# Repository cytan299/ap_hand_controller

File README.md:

# A simple hand controller for Astro-Physics mounts

by C.Y. Tan 2018

It is well-known, that the new GTOCP4 control box can be controlled
with a phone or a pad. However, I really like the feel of real buttons
in a controller rather than using "virtual" buttons on a phone or pad.
This means that the only solution that Astro-Physics (AP) has for people like
me is to buy their AP keypad.

If I had the AP keypad, I will mainly use it for Polar aligning with
PoleMaster and for recalibrating (which is the same as syncing for all
other mounts). After polar alignment and recalibrating, PHD2 will be
used for guiding the scope. Therefore, the AP keypad will only be used
at the start of my imaging session, and no more. Thus, it is hard for
me to justify spending $1000 for an AP keypad when I will hardly use.
I had to figure out a solution.

And here's my solution:
* I have built a simple hand controller for my Mach1GTO. Its purpose
is **not** to replace the AP keypad because it does not initialize the
CP4, have any star database or goto capability etc. My goal is to just
move the mount for calibrating the mount to a star and be compatible
with PoleMaster.

## Design

The goal of my hand controller is to be low cost (less than $200). The
simplest way I know how to do this is to base it on an
[Arduino controller](https://www.sparkfun.com/products/12640). The
other low cost components are

* A small 64x48
  [OLED display](https://www.ebay.com/itm/0-66-OLED-Display-Module-7pin-64x48-Screen-SPI-I2C-3-3-5V-for-Arduino-AVR-STM32/311968961516?_trkparms=aid%3D111001%26algo%3DREC.SEED%26ao%3D1%26asc%3D51025%26meid%3Dd4485726d0e34c16a699dcc92951db6e%26pid%3D100675%26rk%3D5%26rkt%3D15%26sd%3D323141166313%26itm%3D311968961516&_trksid=p2481888.c100675.m4236&_trkparms=pageci%3Ada1189f9-3ac9-11e8-906e-74dbd1800d52%7Cparentrq%3Aa2cf6cb51620ab6ac78552f3fffc49d7%7Ciid%3A1)
  for showing the user options and the state of the controller.
* A [thumb joystick](https://www.sparkfun.com/products/9032) for
selecting menu items and for moving the telescope in RA and DEC.
* The hand controller will be connected to the same port that the AP
  keypad uses. 

## Support

This is unsupported hardware. Build at your own peril! :)

You can submit questions or bug reports using the
[issues](https://github.com/cytan299/ap_hand_controller/issues) tab on
the right and then click on **NEW**.

Have fun!

## Directory structure

* **howto** Assembly instructions for the hand controller.
* **ponoko** The files that are used for laser cutting the acrylic parts of
the design. These files can be sent directly to
[Ponoko](http://www.ponoko.com) for laser cutting.
* **bom** Bill of materials for one hand controller.
* **eagle** Eagle schematic and board files.
* **arduino** Source code for the hand controller.
* **pics** Photographs used in the README's and Wiki.
* **user manual** contains the hand controller user manual.

## Other information

More information can be found in he *README.md* files in each
directory and the [wiki](https://github.com/cytan299/ap_hand_controller/wiki/A-simple-hand-controller-for-Astro-Physics-mounts) of this project on github.

## Copyright
All the software, documentation, and hardware that I have written is
copyright 2018 C.Y. Tan.

All software is released under GPLv3

All documentation is released under:
* Creative Commons Attribution-ShareAlike 3.0 Unported License
* GNU Free Documentation License, Version 1.3
* Creative Commons Attribution-ShareAlike 4.0 International License

All hardware is released under CERN Hardware Open License v1.2

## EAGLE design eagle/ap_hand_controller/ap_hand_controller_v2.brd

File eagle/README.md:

# Eagle files

These are the eagle files that can be sent to pc board manufacturers to
be made. There is a free version of [eagle](http://cadsoftusa.com)
that can be downloaded to view the designs.

## Directories

* **ap_hand_controller** The hand controller unit schematic and pcb.

## Copyright

The schematic and board designs are copyright 2018 C.Y. Tan and
released under the CERN Open Hardware License v1.2

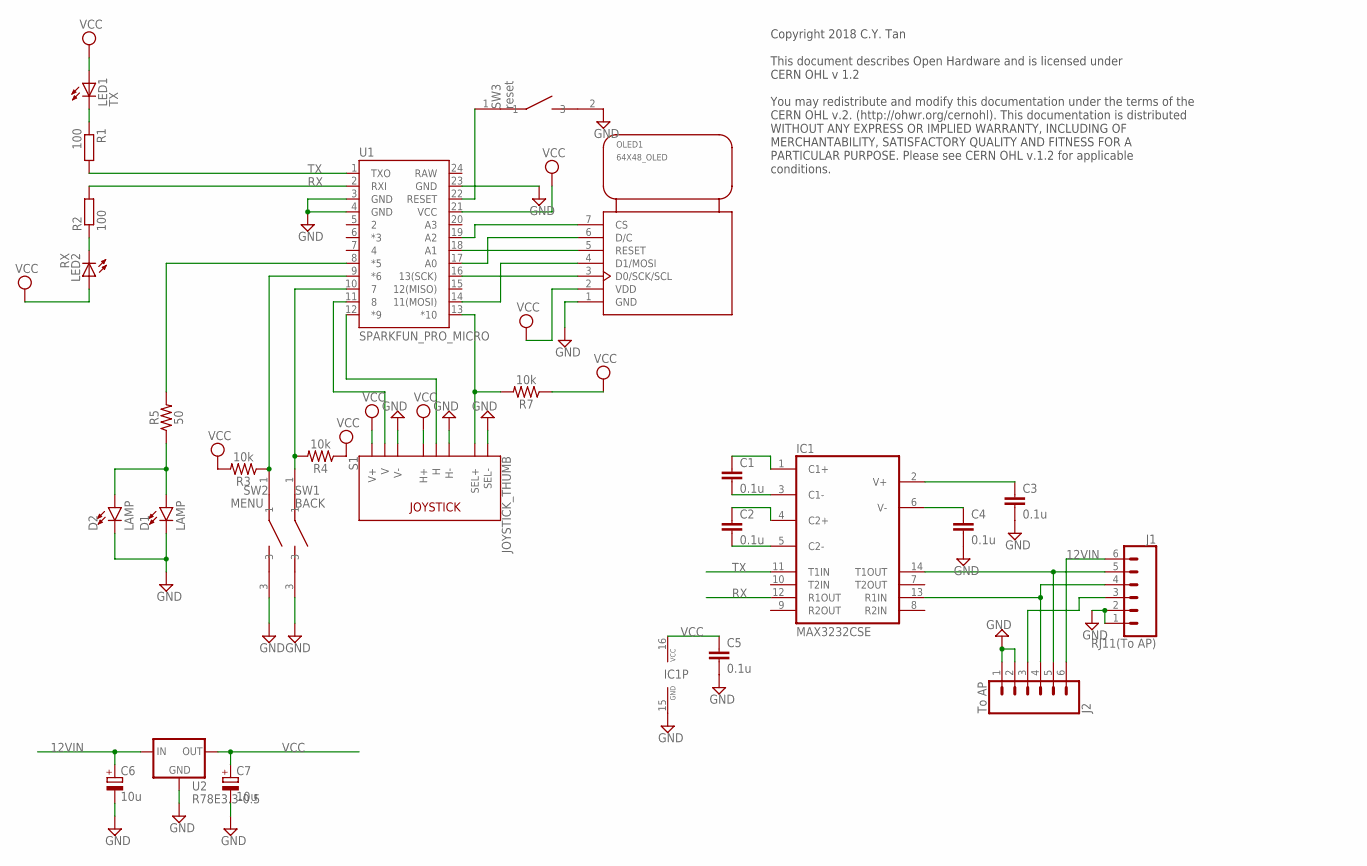
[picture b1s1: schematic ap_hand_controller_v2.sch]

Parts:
C1, C2, C3, C4, C5: 0.1u; C1206
C6, C7: 10u; E2,5-6
D1, D2: LAMP; LED_5MM
IC1: MAX3232CSE; SO16
J1: RJ11(To AP); RJ11-6
J2: To AP; 1X06_NO_SILK
LED1: TX; CHIPLED_1206
LED2: RX; CHIPLED_1206
OLED1: 64X48_OLED
R1, R2: 100; R0805
R3, R4, R7: 10k; AXIAL-0.3
R5: 50; AXIAL-0.3
S1: JOYSTICK_THUMB; JOYSTICK
SW1: BACK; TSA12110_TACT_SWITCH
SW2: MENU; TSA12110_TACT_SWITCH
SW3: reset; TACTILE_SWITCH_90DEG
U1: SPARKFUN_PRO_MICRO
U2: R78E3.3-0.5; DC-DC_CONVERTER_78XX

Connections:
12VIN: C6.+, J1.6, J2.6, U2.VIN (IN)
GND: C3.2, C4.2, C5.2, C6.-, C7.-, D1.K (C), D2.K (C), IC1.15 (GND), J1.1, J1.2, J2.1, J2.2, OLED1.1 (GND), S1.B2A (SEL-), S1.H3 (H-), S1.V3 (V-), SW1.3, SW2.3, SW3.2 (3), U1.3 (GND), U1.4 (GND), U1.23 (GND), U2.GND
unnamed: C1.1, IC1.1 (C1+)
unnamed: C1.2, IC1.3 (C1-)
unnamed: C2.1, IC1.4 (C2+)
unnamed: C2.2, IC1.5 (C2-)
unnamed: C4.1, IC1.6 (V-)
unnamed: C3.1, IC1.2 (V+)
unnamed: IC1.14 (T1OUT), J1.5, J2.5
unnamed: IC1.13 (R1IN), J1.4, J2.4
unnamed: LED1.C, R1.1
unnamed: LED2.C, R2.1
unnamed: S1.V2 (V), U1.11 (8)
unnamed: S1.H2 (H), U1.12 (*9)
unnamed: SW3.1, U1.22 (RESET)
unnamed: OLED1.3 (D0/SCK/SCL), U1.16 (13(SCK))
unnamed: OLED1.6 (D/C), U1.17 (A0)
unnamed: OLED1.4 (D1/MOSI), U1.14 (11(MOSI))
unnamed: OLED1.5 (RESET), U1.18 (A1)
unnamed: OLED1.7 (CS), U1.19 (A2)
unnamed: R4.P$2 (2), SW1.1, U1.10 (7)
unnamed: R3.P$1 (1), SW2.1, U1.9 (*6)
unnamed: D1.A, D2.A, R5.P$1 (1)
unnamed: R7.P$2 (2), S1.B1A (SEL+), U1.13 (*10)
unnamed: J1.3, J2.3
unnamed: R5.P$2 (2), U1.8 (*5)
RAW: U1.24 (RAW)
RX: IC1.12 (R1OUT), R2.2, U1.2 (RXI)
TX: IC1.11 (T1IN), R1.2, U1.1 (TXO)
VCC: C5.1, C7.+, IC1.16 (VCC), LED1.A, LED2.A, OLED1.2 (VDD), R3.P$2 (2), R4.P$1 (1), R7.P$1 (1), S1.H1 (H+), S1.V1 (V+), U1.21 (VCC), U2.VOUT (OUT)

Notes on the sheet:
Copyright 2018 C.Y. Tan This document describes Open Hardware and is licensed under CERN OHL v 1.2 You may redistribute and modify this documentation under the terms of the CERN OHL v.2. (http://ohwr.org/cernohl). This documentation is distributed WITHOUT ANY EXPRESS OR IMPLIED WARRANTY, INCLUDING 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

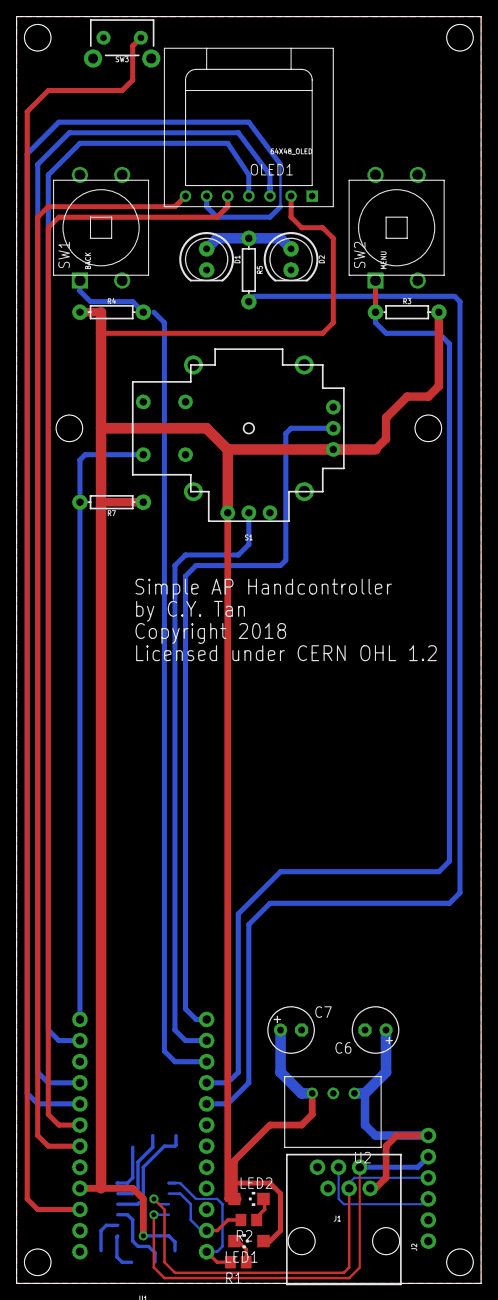
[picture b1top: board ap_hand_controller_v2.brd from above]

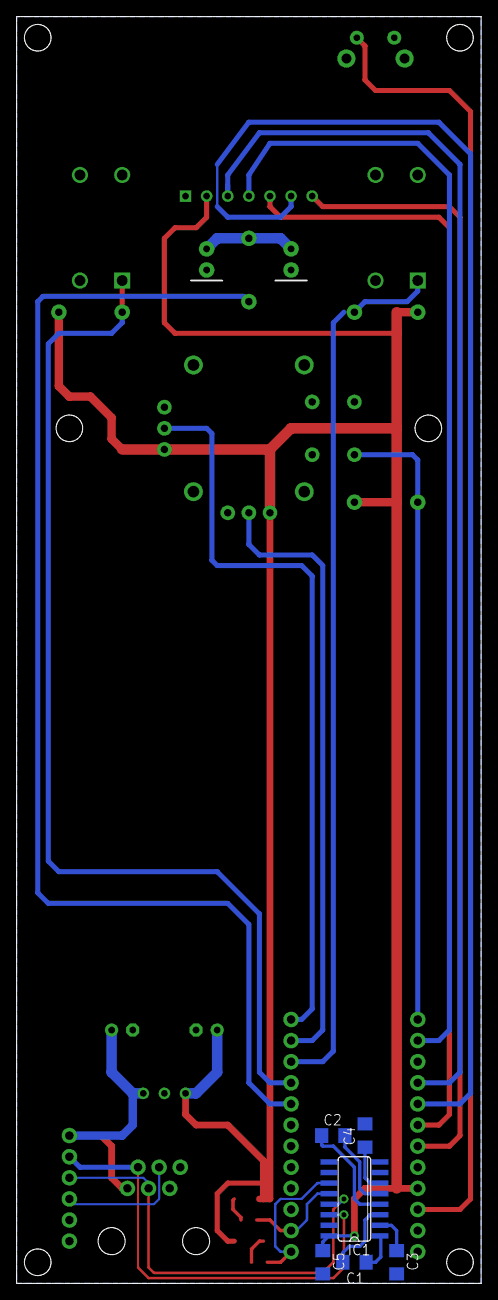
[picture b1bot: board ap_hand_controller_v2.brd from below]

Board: 2 copper layers, 55.9 x 152.4 mm, 27 parts (6 on the bottom side), 29 nets.

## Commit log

2018-07-29 A simple handcontroller for Astro-Physics mounts
2018-07-29 Updated README.md to have the correct paths. Added photo to pics
2018-07-29 pics: reduced size of closed_small.jpg
2018-07-29 Updated REAME.md
2018-07-29 Updated arduino/hand_controller
2018-07-29 First try to fix arduino/hand_controller access problem by removing it
2018-07-29 Hopefully now arduino/hand_controller is accessible
2018-07-29 removed arduino/hand_controller
2018-07-29 removed arduino subdirectory
2018-07-29 Re-added arduino subdirectory
2018-07-29 Removed arduino/hand_controller again
2018-07-30 arduio/hand_controller subdirectory should now be accessible
2018-07-30 One more time ...
2018-07-30 Added README.md to bom directory
2018-08-12 Updated arduino/handcontroller code to swap East and West keys so that behaviour is in the usual convention
2018-08-16 bom: updated bill of materials
2018-09-02 arduino: Major improvement. Joystick pushbutton now uses an interrupt to make response time faster.
2018-09-02 arduino: improved responsiveness of joystick of handcontroller.
2018-09-03 Updated hand_controller.ino loop() comments
2018-09-03 Added user manual and updated README.md's
2018-09-03 user manual typos corrected
2018-09-04 Fixed wiki link in README.md
2019-05-26 Updated user manual to include when RESET has to be pressed.
2021-01-07 bom.ods: Updated components without Digikey part numbers.
2021-03-28 Fixed Vcc unconnected bug in ap_hand_controller_v2.brd. Thanks to Andrew (ab15Kath) for discovering this bug.
2025-07-31 bom/updated link for OLED source
2025-08-01 bom/bom.ods updated link to where to purchase OLED

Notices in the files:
eagle/ap_hand_controller/ap_hand_controller_v2.brd:
Licensed under CERN OHL 1.2
eagle/ap_hand_controller/ap_hand_controller_v2.sch:
PARTICULAR PURPOSE. Please see CERN OHL v.1.2 for applicable
parts and their libraries:
SparkFun-Boards: Licensing: Creative Commons ShareAlike 4.0 International - https://creativecommons.org/licenses/by-sa/4.0
